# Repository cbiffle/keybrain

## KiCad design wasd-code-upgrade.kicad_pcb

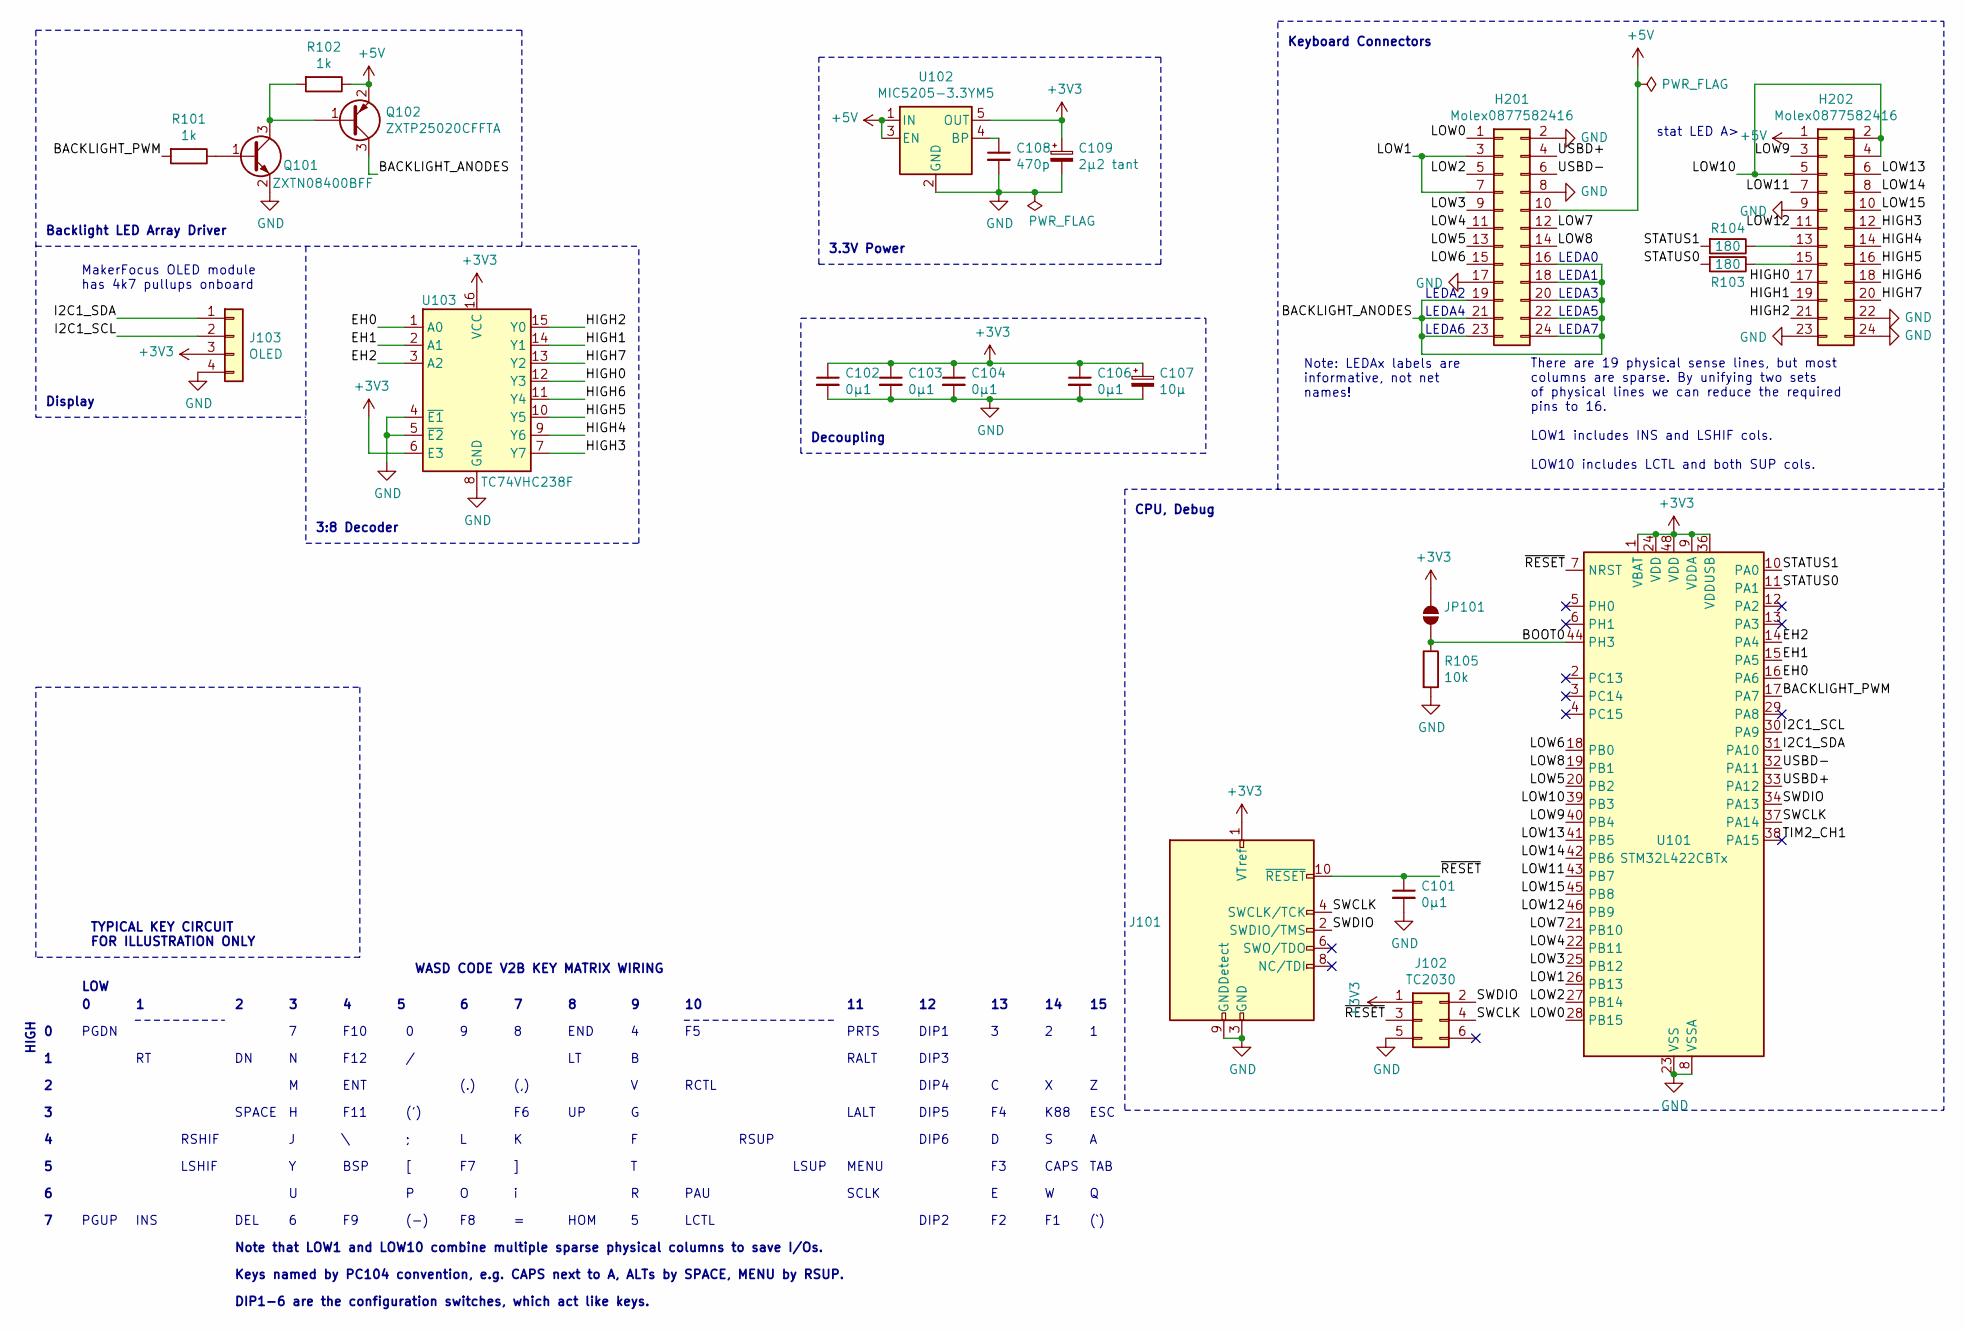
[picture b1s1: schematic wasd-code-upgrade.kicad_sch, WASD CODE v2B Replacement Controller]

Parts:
C101, C102, C103, C104, C106: 0µ1; C_0603_1608Metric
C107: 10µ; C_0603_1608Metric
C108: 470p; C_0603_1608Metric
C109: 2µ2 tant; C_0603_1608Metric
H201, H202: Molex0877582416; PinHeader_2x12_P2.00mm_Vertical
J101: Conn_ARM_JTAG_SWD_10; PinHeader_2x05_P1.27mm_Vertical_SMD
J102: TC2030; Tag-Connect_TC2030-IDC-NL_2x03_P1.27mm_Vertical
J103: OLED; PinSocket_1x04_P2.54mm_Vertical_SMD_Pin1Left
JP101: SolderJumper_2_Open; SolderJumper-2_P1.3mm_Open_RoundedPad1.0x1.5mm
Q101: ZXTN08400BFF; SOT-23
Q102: ZXTP25020CFFTA; SOT-23
R101, R102: 1k; R_0603_1608Metric
R103, R104: 180; R_0603_1608Metric
R105: 10k; R_0603_1608Metric
U101: STM32L422CBTx; LQFP-48_7x7mm_P0.5mm
U102: MIC5205-3.3YM5; SOT-23-5
U103: TC74VHC238F; VSSOP-16_3.0x4.25mm_P0.5mm

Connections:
+3V3: C102.1, C103.1, C104.1, C106.1, C107.1, C109.1, J101.1 (VTref), J102.1, J103.3, JP101.1 (A), U101.1 (VBAT), U101.9 (VDDA), U101.24 (VDD), U101.36 (VDDUSB), U101.48 (VDD), U102.5 (OUT), U103.6 (E3), U103.16 (VCC)
+5V: H201.10, H202.1, Q102.2 (E), R102.1, U102.1 (IN), U102.3 (EN)
/BACKLIGHT_ANODES: H201.16, H201.18, H201.19, H201.20, H201.21, H201.22, H201.23, H201.24, Q102.3 (C)
/BACKLIGHT_PWM: R101.2, U101.17 (PA7)
/BOOT0: JP101.2 (B), R105.1, U101.44 (PH3)
/EH0: U101.16 (PA6), U103.1 (A0)
/EH1: U101.15 (PA5), U103.2 (A1)
/EH2: U101.14 (PA4), U103.3 (A2)
/HIGH0: H202.17, U103.12 (Y3)
/HIGH1: H202.19, U103.14 (Y1)
/HIGH2: H202.21, U103.15 (Y0)
/HIGH3: H202.12, U103.7 (Y7)
/HIGH4: H202.14, U103.9 (Y6)
/HIGH5: H202.16, U103.10 (Y5)
/HIGH6: H202.18, U103.11 (Y4)
/HIGH7: H202.20, U103.13 (Y2)
/I2C1_SCL: J103.2, U101.30 (PA9)
/I2C1_SDA: J103.1, U101.31 (PA10)
/LOW0: H201.1, U101.28 (PB15)
/LOW1: H201.3, H201.7, U101.26 (PB13)
/LOW2: H201.5, U101.27 (PB14)
/LOW3: H201.9, U101.25 (PB12)
/LOW4: H201.11, U101.22 (PB11)
/LOW5: H201.13, U101.20 (PB2)
/LOW6: H201.15, U101.18 (PB0)
/LOW7: H201.12, U101.21 (PB10)
/LOW8: H201.14, U101.19 (PB1)
/LOW9: H202.3, U101.40 (PB4)
/LOW10: H202.2, H202.4, H202.5, U101.39 (PB3)
/LOW11: H202.7, U101.43 (PB7)
/LOW12: H202.11, U101.46 (PB9)
/LOW13: H202.6, U101.41 (PB5)
/LOW14: H202.8, U101.42 (PB6)
/LOW15: H202.10, U101.45 (PB8)
/STATUS0: R103.2, U101.11 (PA1)
/STATUS1: R104.2, U101.10 (PA0)
/SWCLK: J101.4 (SWCLK/TCK), J102.4, U101.37 (PA14)
/SWDIO: J101.2 (SWDIO/TMS), J102.2, U101.34 (PA13)
/TIM2_CH1: U101.38 (PA15)
/USBD+: H201.4, U101.33 (PA12)
/USBD-: H201.6, U101.32 (PA11)
/~RESET: C101.1, J101.10 (~RESET), J102.3, U101.7 (NRST)
GND: C101.2, C102.2, C103.2, C104.2, C106.2, C107.2, C108.2, C109.2, H201.2, H201.8, H201.17, H202.9, H202.22, H202.23, H202.24, J101.3 (GND), J101.5 (GND), J101.9 (GNDDetect), J102.5, J103.4, Q101.2 (E), R105.2, U101.8 (VSSA), U101.23 (VSS), U101.35 (VSS), U101.47 (VSS), U102.2 (GND), U103.4 (~E1), U103.5 (~E2), U103.8 (GND)
unnamed: C108.1, U102.4 (BP)
unnamed: H202.13, R104.1
unnamed: H202.15, R103.1
unnamed: Q101.1 (B), R101.1
unnamed: Q101.3 (C), Q102.1 (B), R102.2

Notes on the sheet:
LEDA6
(-)
LCTL
LALT
(,)
END
INS
DIP6
LEDA0
DIP2
LEDA2
Keys named by PC104 convention, e.g. CAPS next to A, ALTs by SPACE, MENU by RSUP.
Note that LOW1 and LOW10 combine multiple sparse physical columns to save I/Os.
DIP3
(`)
DIP1-6 are the configuration switches, which act like keys.
(')
RSHIF
LSHIF
LEDA7
DIP5
RCTL
SCLK
DEL
K88
PRTS
Backlight LED Array Driver
3.3V Power
LEDA3
CAPS
WASD CODE V2B KEY MATRIX WIRING
TAB
TYPICAL KEY CIRCUIT FOR ILLUSTRATION ONLY
Display
LEDA4
PAU
LEDA1
F11
There are 19 physical sense lines, but most columns are sparse. By unifying two sets of physical lines we can reduce the required pins to 16. LOW1 includes INS and LSHIF cols. LOW10 includes LCTL and both SUP cols.
DIP1

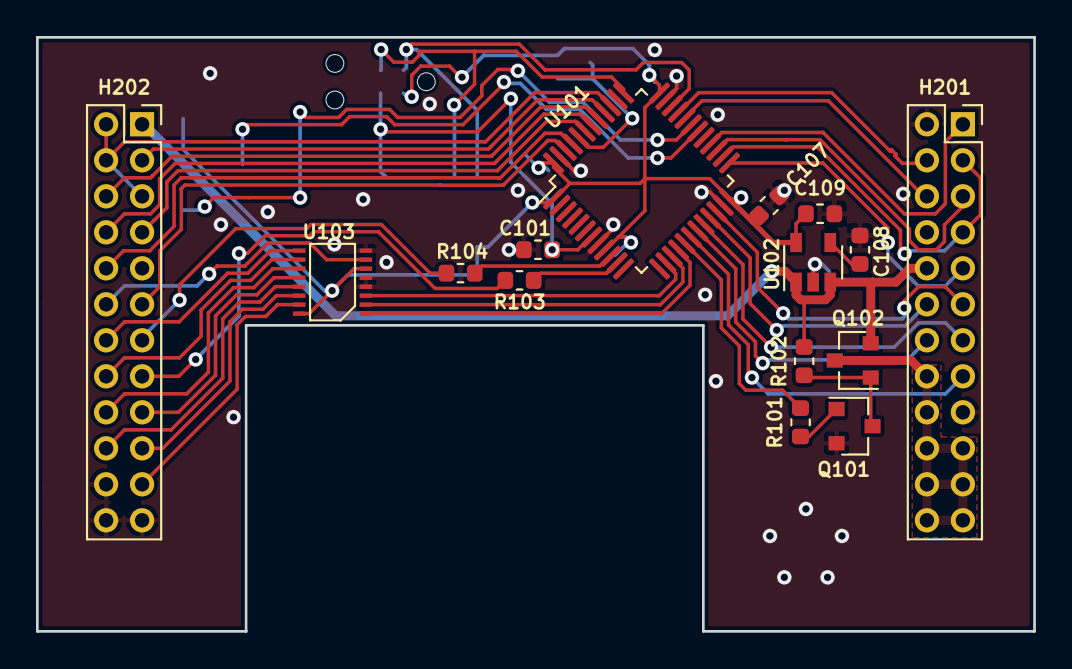
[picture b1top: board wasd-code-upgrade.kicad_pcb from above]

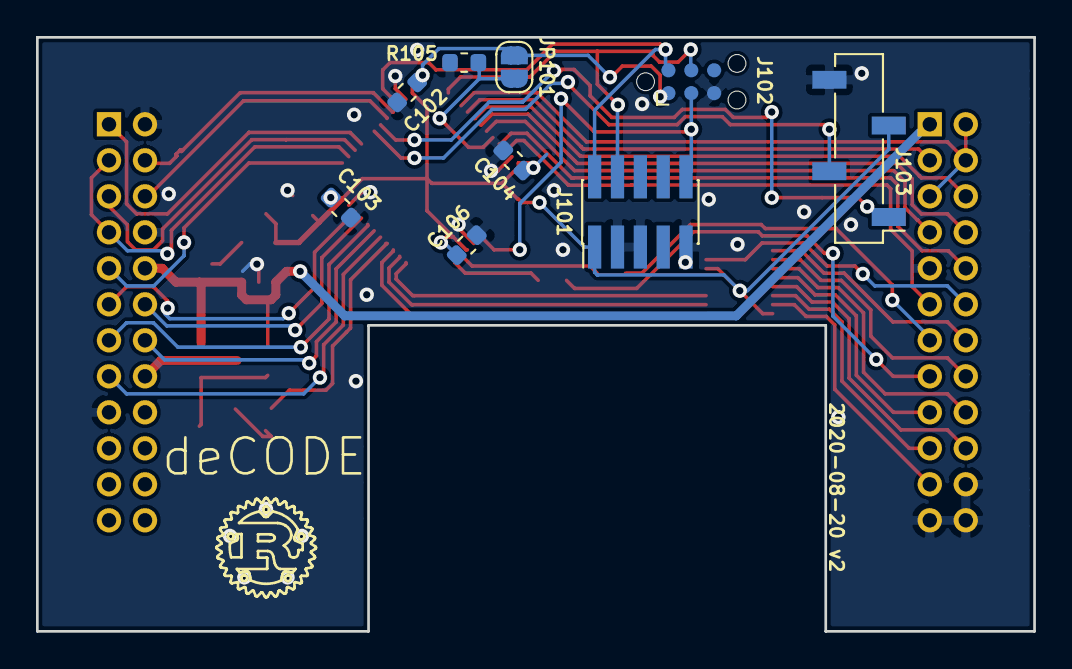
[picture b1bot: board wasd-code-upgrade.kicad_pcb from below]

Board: 2 copper layers, 55.4 x 33.0 mm, 24 parts (9 on the bottom side), 47 nets.

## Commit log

2020-08-03 fourk/fw
2020-08-03 USB refactor WIP
2020-08-03 fourk: assorted
2020-08-03 WIP fw abstract
2020-08-03 fourk/fw: dispatch
2020-08-03 fourk: refactor descriptor reads
2020-08-04 fourk/fw: descriptor struct cleanup
2020-08-04 fourk/fw: don't use copy_nonoverlapping on USBSRAM
2020-08-04 fourk/fw: get descriptor refactor
2020-08-04 fourk: forgot to commit pcb??
2020-08-07 fourk/fw: use linker to lay out USBSRAM
2020-08-09 fourk/fw: start factoring out USB driver
2020-08-09 fourk/fw: continue factoring out driver
2020-08-09 fourk/fw: hid -> module
2020-08-10 fourk/fw: add Set_Protocol support
2020-08-10 fourk/fw: scan matrix with DMA
2020-08-10 fourk/fw: factor out scan
2020-08-10 fourk/fw: document boot keyboard descriptor
2020-08-10 fourk/fw: generalize to more scan rows
2020-08-10 fourk/fw: timing outputs on GPIOC
2020-08-12 wasd-code-upgrade
2020-08-12 wasd-code-upgrade: schematic polish, matrix table
2020-08-15 wasd-code-upgrade: v2 layout
2020-08-15 wasd-code-upgrade: high side decoder simplifies routing
2020-08-15 wasd-code-upgrade: socket for MakerFocus OLED
2020-08-15 wasd-code-upgrade: tidy schematic
2020-08-21 wasd-code-upgrade: rework after playing with v1
    - Move _very bright_ status LEDs to PWM-capable pins.
    - Fix mistakes in matrix.
    - Simplify some layout to move more things to topside.
2020-08-21 Fixes for standalone repo.
2020-08-21 wasd-code-upgrade: remove now-unused SOICbite lib
2020-08-21 README update
2020-08-21 srch README
2020-08-21 fw: updates for full CODE matrix with basic Fn layer
2020-08-22 fw: add feature for distinguishing v1/v2 boards
2020-08-22 fw: insert some barriers
2020-08-22 Simplify running firmware
2020-08-22 fw: readme
2020-08-22 fw: implement debouncing.
2020-08-22 fw: remove more diagnostic toggling
2020-08-22 fw: use panic_halt
2020-08-22 fw: demote some asserts not required for safety to debug
2020-08-22 fw: reduce size by eliminating panic sites with msgs
2020-08-22 fw: simplify SOF status bit clear
2020-08-22 fw: preliminary suspend-resume hacking
2020-08-22 srch: add omitted gitignore
2020-08-22 fw: factor kbd out
2020-08-22 fw: slightly ugly LED support
2020-08-23 fw: backlight toggle with fn+f12
2020-08-23 fw: add DFU entry keystroke
2020-08-25 fw: DIP4: RA -> Cp
2020-08-29 fw: extend debounce interval to 10ms after some repeats
2024-06-06 Clean up warnings on modern Rust.
2024-06-06 Fix Clippy warnings.
